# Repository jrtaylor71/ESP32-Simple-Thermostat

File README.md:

# ESP32 Simple Thermostat

A comprehensive, feature-rich thermostat system built on the ESP32 platform with professional PCB design. Perfect for DIY smart home automation with full Home Assistant integration.

## 🌟 Key Features

- **📱 Local Touch Control**: ILI9341 TFT LCD with intuitive touch interface
- **🏠 Smart Home Ready**: Full MQTT integration with Home Assistant auto-discovery
- **🌡️ Dual Sensors**: DHT11 for ambient conditions + DS18B20 for hydronic systems
- **⚡ Multi-Stage HVAC**: Support for 2-stage heating and cooling systems
- **💨 Advanced Fan Control**: Auto, continuous, and scheduled cycling modes
- **🌐 Web Interface**: Complete web-based configuration and monitoring
- **📡 Offline Operation**: Full functionality without WiFi connection
- **🔧 Professional PCB**: Custom PCB design for clean, permanent installation
- **🔄 OTA Updates**: Over-the-air firmware updates
- **🔒 Factory Reset**: Built-in reset capability via boot button

## 🚀 Quick Start

### Hardware Requirements
- ESP32 WROOM-32 Development Board
- ILI9341 320x240 TFT LCD Touch Display
- DHT11 Temperature/Humidity Sensor (digital pin)
- DS18B20 Temperature Sensor (optional, for hydronic heating)
- 6x Relay Module (5 HVAC + 1 hydronic pump)
- Custom PCB (files included) or breadboard for prototyping

### Software Setup
1. Install [PlatformIO](https://platformio.org/) IDE
2. Clone this repository
3. Open project in PlatformIO
4. Build and upload to ESP32
5. Use touch interface to configure WiFi and settings

### Pin Configuration

#### TFT Display (ILI9341)
```cpp
#define TFT_MISO 19    // SPI MISO
#define TFT_MOSI 23    // SPI MOSI
#define TFT_SCLK 18    // SPI Clock
#define TFT_CS   15    // Chip Select
#define TFT_DC    2    // Data/Command
#define TFT_RST   5    // Reset
#define TFT_BL   32    // Backlight (PWM)
#define TOUCH_CS  4    // Touch Chip Select
```

#### Sensors
```cpp
#define DHTPIN 22           // DHT11 data pin
#define ONE_WIRE_BUS 27     // DS18B20 data pin (optional)
```

#### Relay Outputs
```cpp
const int heatRelay1Pin = 13;   // Stage 1 heating
const int heatRelay2Pin = 12;   // Stage 2 heating
const int coolRelay1Pin = 14;   // Stage 1 cooling
const int coolRelay2Pin = 26;   // Stage 2 cooling
const int fanRelayPin = 25;     // Fan control
const int pumpRelayPin = 33;    // Hydronic pump control
```

## 💻 Web Interface

Access the thermostat's web interface by navigating to its IP address:

### Status Page

Real-time monitoring of:
- Current temperature and humidity
- Thermostat and fan modes
- Relay states
- System status

### Settings Page

Complete configuration interface for:
- Temperature setpoints and control modes
- MQTT/Home Assistant integration
- WiFi network settings
- Multi-stage HVAC parameters
- Hydronic heating controls
- Fan scheduling options

## 🏠 Home Assistant Integration

Automatic discovery and integration with Home Assistant:

1. Enable MQTT in thermostat settings
2. Configure MQTT broker details
3. Thermostat appears automatically in Home Assistant
4. Full control via Home Assistant interface
5. Supports climate entity with heating/cooling modes

### MQTT Topics
- **Commands**: `esp32_thermostat/mode/set`, `esp32_thermostat/target_temperature/set`
- **Status**: `esp32_thermostat/current_temperature`, `esp32_thermostat/mode`
- **Discovery**: Automatic Home Assistant device discovery

## 🔧 Professional PCB

The project includes a complete custom PCB design:

### PCB Features
- Professional 4-layer design
- All components integrated on single board
- Labeled terminal blocks for easy HVAC wiring
- Proper grounding and signal integrity
- Standard mounting holes for enclosure installation

### Manufacturing Files
Complete manufacturing package in `ESP32-Simple-Thermostat-PCB/jlcpcb/`:
- Gerber files for PCB fabrication
- Drill files for via and hole placement
- Bill of Materials (BOM) for component sourcing
- Component Placement List (CPL) for assembly

## 📖 Documentation

- **[Complete Documentation](DOCUMENTATION.md)**: Comprehensive technical documentation
- **[Copilot File](.copilot)**: GitHub Copilot context for development
- **Inline Comments**: Extensive code documentation
- **Serial Debug**: Detailed debug output for troubleshooting

## 🛠️ Advanced Features

### Multi-Stage Operation
- Intelligent staging based on time and temperature
- Configurable stage 2 activation parameters
- Prevents system short-cycling
- Optimizes energy efficiency

### Hydronic Heating Support
- DS18B20 water temperature monitoring
- Safety interlocks prevent operation when water is too cold
- Configurable high/low temperature thresholds
- Perfect for radiant floor heating systems

### Fan Control Options
- **Auto**: Fan runs only with heating/cooling
- **On**: Continuous fan operation
- **Cycle**: Scheduled fan operation (configurable minutes per hour)

### Safety Features
- Watchdog timer prevents system lockups
- Factory reset via boot button (10+ seconds)
- Temperature limit enforcement
- Graceful offline operation

## 🔧 Factory Reset

Press and hold the boot button for more than 10 seconds while the thermostat is running to restore all settings to defaults.

## 📄 License

This project is released under the GNU General Public License v3.0. Free to use, modify, and distribute.

## 🤝 Contributing

Contributions welcome! Please:
1. Fork the repository
2. Create a feature branch
3. Make your changes
4. Submit a pull request

## 📞 Support

- **Issues**: Use GitHub Issues for bug reports
- **Discussions**: GitHub Discussions for questions
- **Documentation**: Comprehensive docs included
- **Serial Debug**: Detailed logging at 115200 baud

## ⭐ Version

**Current Version**: 1.1.0
- Complete thermostat functionality
- MQTT/Home Assistant integration with auto-discovery
- 7-day scheduling system
- Multi-stage HVAC support with hydronic pump
- DHT11 sensor support
- PCB design
- Web interface and OTA updates

---

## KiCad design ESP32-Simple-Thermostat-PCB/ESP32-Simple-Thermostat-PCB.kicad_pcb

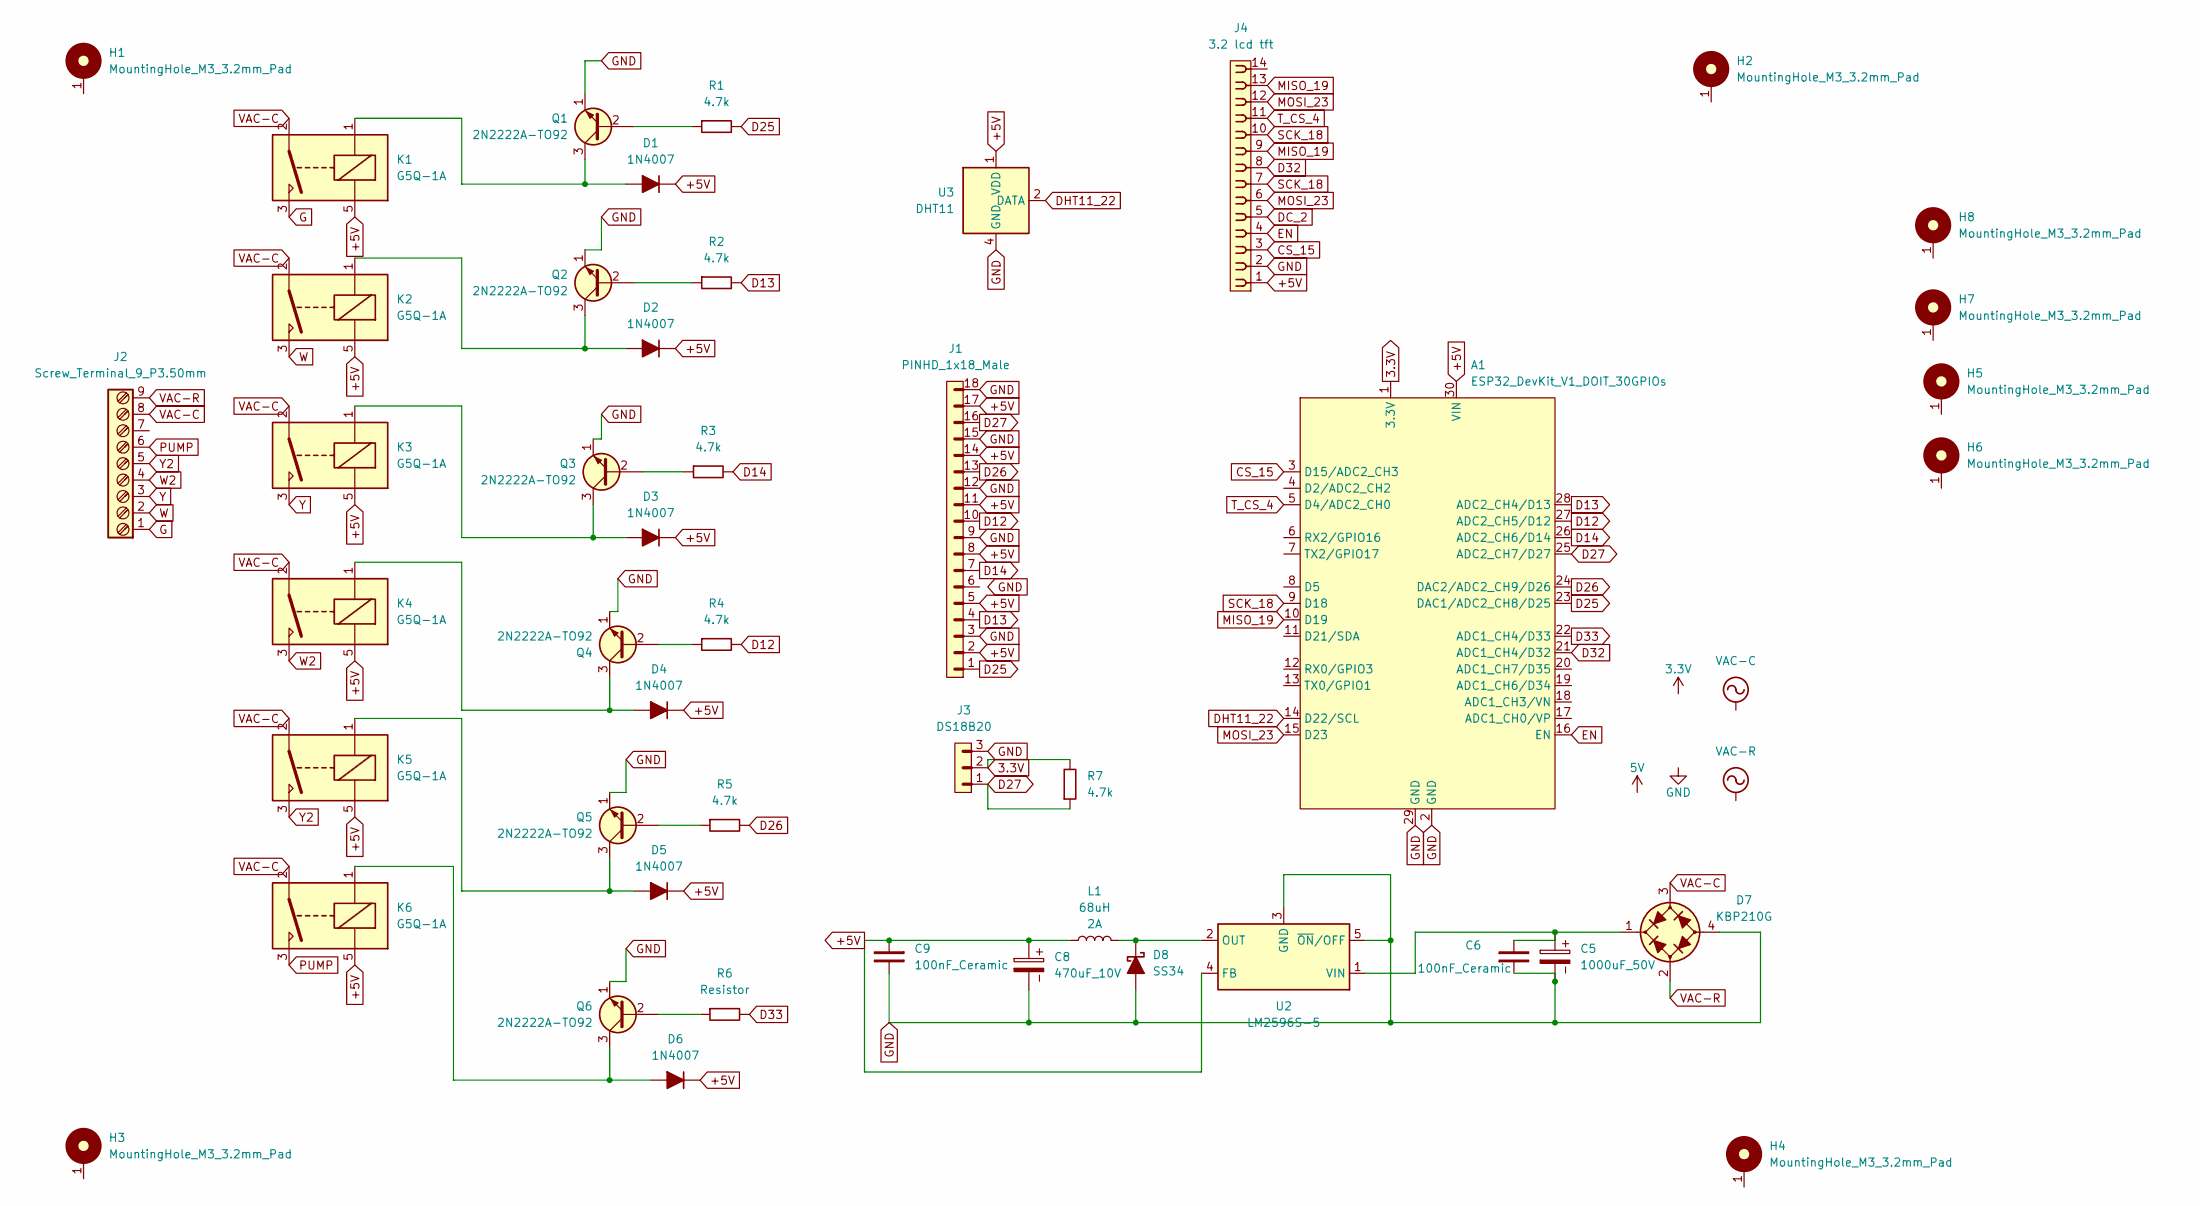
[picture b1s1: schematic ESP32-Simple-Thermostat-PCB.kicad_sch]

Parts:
A1: ESP32_DevKit_V1_DOIT_30GPIOs; DOIT_ESP32_DEVKIT_30Pins
C5: 1000uF_50V; CP_Radial_D16.0mm_P7.50mm
C6, C9: 100nF_Ceramic; C_Disc_D5.0mm_W2.5mm_P2.50mm
C8: 470uF_10V; CP_Radial_D8.0mm_P3.50mm
D1, D2, D3, D4, D5, D6: 1N4007; D_DO-41_SOD81_P7.62mm_Horizontal
D7: KBP210G; Diode_Bridge_KBP
D8: SS34; D_SMC
H1, H2, H3, H4, H5, H6, H7, H8: MountingHole_M3_3.2mm_Pad; MountingHole_3.2mm_Pad
J1: PINHD_1x18_Male; PinHeader_1x18_P2.54mm_Vertical
J2: Screw_Terminal_9_P3.50mm; TerminalBlock_Phoenix_PT-1,5-9-3.5-H_1x09_P3.50mm_Horizontal
J3: DS18B20; PinHeader_1x03_P2.54mm_Vertical
J4: 3.2 lcd tft; PinSocket_1x14_P2.54mm_Vertical
K1, K2, K3, K4, K5, K6: G5Q-1A; Relay_SPST_Omron-G5Q-1A
L1: 12uH_5.2A_1260; L_Bourns_SRR1260; Part Number SRR1260-120M
Q1, Q2, Q3, Q4, Q5, Q6: 2N2222A-TO92; TO-92_Inline_Wide_EBC
R1, R2, R3, R4, R5, R7: 4.7k; R_Axial_DIN0207_L6.3mm_D2.5mm_P10.16mm_Horizontal
R6: Resistor; R_Axial_DIN0207_L6.3mm_D2.5mm_P10.16mm_Horizontal
U2: LM2596S-5; TO-263-5_TabPin3
U3: DHT11; Aosong_DHT11_5.5x12.0_P2.54mm

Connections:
3.3V: A1.1 (3.3V), J3.2, R7.2
+5V: A1.30 (VIN), C8.1, C9.1, D1.1 (K), D2.1 (K), D3.1 (K), D4.1 (K), D5.1 (K), D6.1 (K), J1.2, J1.5, J1.8, J1.11, J1.14, J1.17, J4.1, K1.5, K2.5, K3.5, K4.5, K5.5, K6.5, L1.1, U2.4 (FB), U3.1 (VDD)
CS_15: A1.3 (D15/ADC2_CH3), J4.3
D12: A1.27 (ADC2_CH5/D12), J1.10, R4.2
D13: A1.28 (ADC2_CH4/D13), J1.4, R2.2
D14: A1.26 (ADC2_CH6/D14), J1.7, R3.2
D25: A1.23 (DAC1/ADC2_CH8/D25), J1.1, R1.2
D26: A1.24 (DAC2/ADC2_CH9/D26), J1.13, R5.2
D27: A1.25 (ADC2_CH7/D27), J1.16, J3.1, R7.1
D32: A1.21 (ADC1_CH4/D32), J4.8
D33: A1.22 (ADC1_CH4/D33), R6.2
DC_2: J4.5
DHT11_22: A1.14 (D22/SCL), U3.2 (DATA)
EN: A1.16 (EN), J4.4
G: J2.1, K1.3
GND: A1.2 (GND), A1.29 (GND), C5.2, C6.1, C8.2, C9.2, D7.4 (-), D8.2 (A), J1.3, J1.9, J1.12, J1.15, J1.18, J3.3, J4.2, Q1.1 (E), Q2.1 (E), Q3.1 (E), Q4.1 (E), Q5.1 (E), Q6.1 (E), U2.3 (GND), U2.5 (~ON/OFF), U3.4 (GND)
MISO_19: A1.10 (D19), J4.9, J4.13
MOSI_23: A1.15 (D23), J4.6, J4.12
unnamed: D1.2 (A), K1.1, Q1.3 (C)
unnamed: D2.2 (A), K2.1, Q2.3 (C)
unnamed: D3.2 (A), K3.1, Q3.3 (C)
unnamed: D4.2 (A), K4.1, Q4.3 (C)
unnamed: D5.2 (A), K5.1, Q5.3 (C)
unnamed: D6.2 (A), K6.1, Q6.3 (C)
unnamed: C5.1, C6.2, D7.1 (+), U2.1 (VIN)
unnamed: D8.1 (K), L1.2, U2.2 (OUT)
unnamed: Q1.2 (B), R1.1
unnamed: Q2.2 (B), R2.1
unnamed: Q3.2 (B), R3.1
unnamed: Q4.2 (B), R4.1
unnamed: Q5.2 (B), R5.1
unnamed: Q6.2 (B), R6.1
PUMP: J2.6, K6.3
SCK_18: A1.9 (D18), J4.7, J4.10
T_CS_4: A1.5 (D4/ADC2_CH0), J4.11
VAC-C: D7.3 (2), J2.8, K1.2, K2.2, K3.2, K4.2, K5.2, K6.2
VAC-R: D7.2 (1), J2.9
W: J2.2, K2.3
W2: J2.4, K4.3
Y: J2.3, K3.3
Y2: J2.5, K5.3

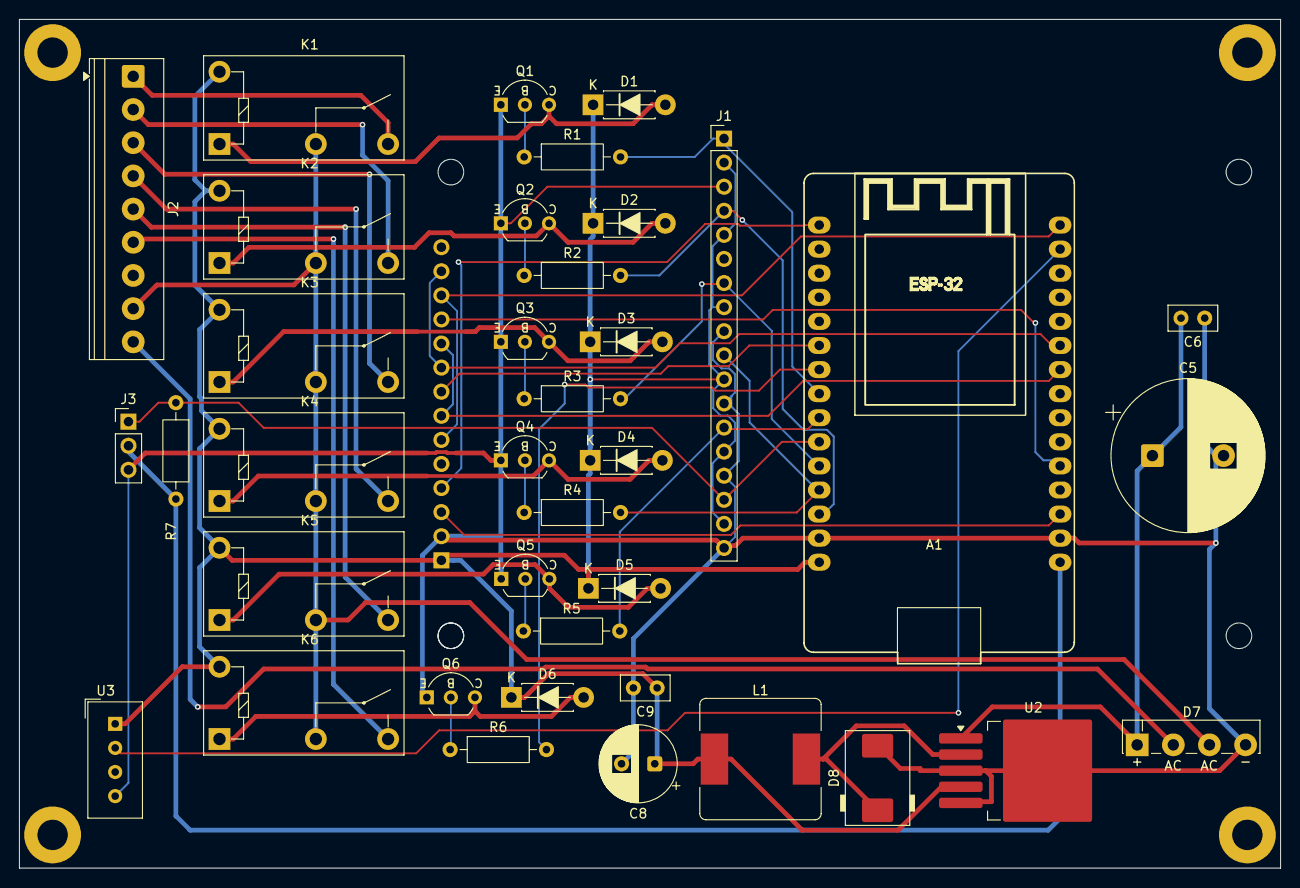
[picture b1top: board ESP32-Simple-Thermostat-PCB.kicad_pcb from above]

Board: 2 copper layers, 133.0 x 89.5 mm, 47 parts (1 on the bottom side), 40 nets.

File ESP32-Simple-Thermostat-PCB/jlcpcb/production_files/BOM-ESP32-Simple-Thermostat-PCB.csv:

Comment,Designator,Footprint,LCSC,Quantity
MountingHole_M3_3.2mm_Pad,H3,MountingHole_3.2mm_Pad,,1
G5Q-1A,K1,Relay_SPST_Omron-G5Q-1A,,1
DHT11,U3,Aosong_DHT11_5.5x12.0_P2.54mm,,1
2N2222A-TO92,Q3,TO-92_Inline_Wide_EBC,,1
G5Q-1A,K6,Relay_SPST_Omron-G5Q-1A,,1
Screw_Terminal_9_P3.50mm,J2,"TerminalBlock_Phoenix_PT-1,5-9-3.5-H_1x09_P3.50mm_Horizontal",,1
1N4007,D4,D_DO-41_SOD81_P7.62mm_Horizontal,,1
External Relays,J1,PinHeader_1x18_P2.54mm_Vertical,,1
MountingHole_M3_3.2mm_Pad,H2,MountingHole_3.2mm_Pad,,1
100nF_Ceramic,C6,C_Disc_D5.0mm_W2.5mm_P2.50mm,,1
4.7k,R7,R_Axial_DIN0207_L6.3mm_D2.5mm_P10.16mm_Horizontal,,1
2N2222A-TO92,Q4,TO-92_Inline_Wide_EBC,,1
1N4007,D3,D_DO-41_SOD81_P7.62mm_Horizontal,,1
1N4007,D2,D_DO-41_SOD81_P7.62mm_Horizontal,,1
2N2222A-TO92,Q5,TO-92_Inline_Wide_EBC,,1
G5Q-1A,K5,Relay_SPST_Omron-G5Q-1A,,1
4.7k,R1,R_Axial_DIN0207_L6.3mm_D2.5mm_P10.16mm_Horizontal,,1
ESP32_DevKit_V1_DOIT_30GPIOs,A1,DOIT_ESP32_DEVKIT_30Pins,,1
1N4007,D5,D_DO-41_SOD81_P7.62mm_Horizontal,,1
G5Q-1A,K2,Relay_SPST_Omron-G5Q-1A,,1
Resistor,R6,R_Axial_DIN0207_L6.3mm_D2.5mm_P10.16mm_Horizontal,,1
MountingHole_M3_3.2mm_Pad,H1,MountingHole_3.2mm_Pad,,1
4.7k,R5,R_Axial_DIN0207_L6.3mm_D2.5mm_P10.16mm_Horizontal,,1
4.7k,R3,R_Axial_DIN0207_L6.3mm_D2.5mm_P10.16mm_Horizontal,,1
470uF_10V,C8,CP_Radial_D8.0mm_P3.50mm,,1
KBP210G,D7,Diode_Bridge_KBP,,1
LM2596S-5,U2,TO-263-5_TabPin3,,1
2N2222A-TO92,Q1,TO-92_Inline_Wide_EBC,,1
1N4007,D1,D_DO-41_SOD81_P7.62mm_Horizontal,,1
2N2222A-TO92,Q6,TO-92_Inline_Wide_EBC,,1
DS18B20,J3,PinHeader_1x03_P2.54mm_Vertical,,1
1N4007,D6,D_DO-41_SOD81_P7.62mm_Horizontal,,1
4.7k,R2,R_Axial_DIN0207_L6.3mm_D2.5mm_P10.16mm_Horizontal,,1
G5Q-1A,K4,Relay_SPST_Omron-G5Q-1A,,1
G5Q-1A,K3,Relay_SPST_Omron-G5Q-1A,,1
100nF_Ceramic,C9,C_Disc_D5.0mm_W2.5mm_P2.50mm,,1
2N2222A-TO92,Q2,TO-92_Inline_Wide_EBC,,1
SS34,D8,D_SMC,,1
MountingHole_M3_3.2mm_Pad,H4,MountingHole_3.2mm_Pad,,1
4.7k,R4,R_Axial_DIN0207_L6.3mm_D2.5mm_P10.16mm_Horizontal,,1
12uH_5.2A_1260,L1,L_Bourns_SRR1260,,1
1000uF_50V,C5,CP_Radial_D16.0mm_P7.50mm,,1
3.2 lcd tft,J4,PinSocket_1x14_P2.54mm_Vertical,,1

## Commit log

2025-01-23 new file: .gitignore new file: .vscode/extensions.json new file: .vscode/settings.json new file: ESP32 Thermostat new file: ESP32-Simple-Thermostat.code-workspace new file: platformio.ini new file: s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
2025-01-23 deleted: ESP32 Thermostat
2025-01-24 modified: platformio.ini modified: src/Main-Thermostat.cpp deleted: src/platformio.ini
2025-01-24 modified: src/Main-Thermostat.cpp
2025-01-27 modified: .pio/build/esp32dev/.sconsign310.dblite modified: .pio/build/esp32dev/FrameworkArduino/firmware_msc_fat.c.o modified: .pio/build/esp32dev/firmware.bin modified: .pio/build/esp32dev/firmware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
2025-01-27 modified: .pio/build/esp32dev/.sconsign310.dblite modified: .pio/build/esp32dev/FrameworkArduino/firmware_msc_fat.c.o modified: .pio/build/esp32dev/firmware.bin modified: .pio/build/esp32dev/firmware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
2025-01-30 modified: .pio/build/esp32dev/.sconsign310.dblite modified: .pio/build/esp32dev/FrameworkArduino/firmware_msc_fat.c.o modified: .pio/build/esp32dev/firmware.bin modified: .pio/build/esp32dev/firmware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
2025-01-30 modified: .pio/build/esp32dev/.sconsign310.dblite modified: .pio/build/esp32dev/FrameworkArduino/firmware_msc_fat.c.o modified: .pio/build/esp32dev/firmware.bin modified: .pio/build/esp32dev/firmware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
2025-02-19 modified: .pio/build/esp32dev/.sconsign310.dblite modified: .pio/build/esp32dev/FrameworkArduino/firmware_msc_fat.c.o modified: .pio/build/esp32dev/firmware.bin modified: .pio/build/esp32dev/firmware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
2025-04-16 Cleanup MQTT
    Improve MQTT integration with Home Assistant.
2025-04-16 more mqtt cleanup
    cleanup published name and temperature increments.
2025-04-16 new file: .pio/build/esp32dev/idedata.json
2025-04-19 modified: .pio/build/esp32dev/.sconsign310.dblite modified: .pio/build/esp32dev/firmware.bin modified: .pio/build/esp32dev/firmware.elf modified: .pio/build/esp32dev/firmware.map modified: .pio/build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
2025-11-20 Initial commit: ESP32 Simple Thermostat project
    - Complete thermostat implementation with web interface
    - MQTT integration with Home Assistant auto-discovery
    - Multi-sensor support (DHT11, DS18B20)
    - TFT touchscreen interface
    - 5-relay HVAC control system
    - Custom PCB design files included
2025-11-23 Standardize project naming to ESP32 Simple Thermostat
    - Updated display text, serial messages, and MQTT device model
    - Updated all web interface page titles and headers
    - Consistent branding across documentation and code
2025-11-24 3d case
2025-11-25 v1.2.0: Apply HIGH and MEDIUM priority improvements from parent project
    HIGH PRIORITY:
    - Add MQTT immediate feedback flag for faster HA responsiveness (~1-1.5s -> <500ms)
    - Fix fan auto mode logic to properly activate with heating/cooling
    MEDIUM PRIORITY:
    - Add guard checks to prevent redundant relay activation calls
    - Fix cooling hysteresis boundary from <= to < for consistency
